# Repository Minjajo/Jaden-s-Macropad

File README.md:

# Jaden-s-Hackpad

This macropad has 16 keys, and right now it just acts as a numpad

This is what it looks like:

## PCB Design:
Here is a picture of my PCB:

Here is a picture of my schematic:

## CAD Design:
(Note: I only designed the case itself. The PCB STEP file was exported from KiCAD and the switches, keycaps, and XIAO were found on GRABCAD)
This is what the assembled hackpad looks like in Fusion:

This is what the case + PCB looks lke in Fusion:

## Bill of Materials:
- 1x SEEEDUINO XIAO RP2040
- 20x through-hole 1N4148 Diodes
- 16x MX-Style switches
- 16x white blank DSA keycaps
- 16x SK6812 MINI-E LEDs
- 4x M3x16mm screws
- Jaden's Custom PCB

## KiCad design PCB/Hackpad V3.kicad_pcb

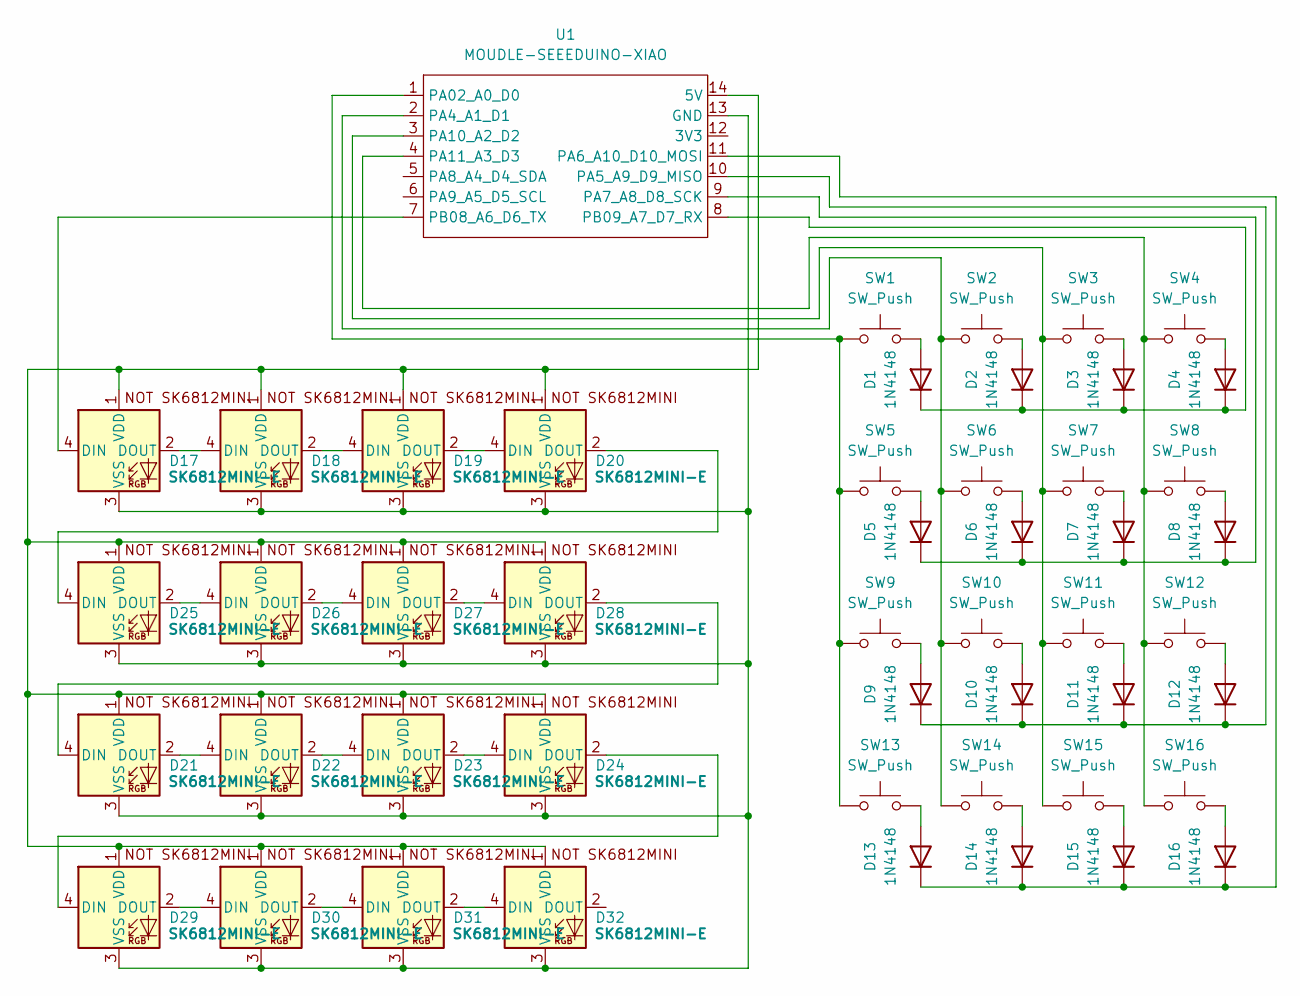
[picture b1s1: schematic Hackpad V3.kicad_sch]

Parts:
D1, D2, D3, D4, D5, D6, D7, D8, D9, D10, D11, D12, D13, D14, D15, D16: 1N4148; D_DO-35_SOD27_P7.62mm_Horizontal
D17, D18, D19, D20, D21, D22, D23, D24, D25, D26, D27, D28, D29, D30, D31, D32: SK6812MINI-E; SK6812MINI-E_fixed
SW1, SW2, SW3, SW4, SW5, SW6, SW7, SW8, SW9, SW10, SW11, SW12, SW13, SW14, SW15, SW16: SW_Push; SW_Cherry_MX_1.00u_PCB
U1: MOUDLE-SEEEDUINO-XIAO; XIAO-Generic-Hybrid-14P-2.54-21X17.8MM

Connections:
unnamed: D1.2 (A), SW1.2
unnamed: D1.1 (K), D2.1 (K), D3.1 (K), D4.1 (K), U1.8 (PB09_A7_D7_RX)
unnamed: D2.2 (A), SW2.2
unnamed: D3.2 (A), SW3.2
unnamed: D4.2 (A), SW4.2
unnamed: D5.2 (A), SW5.2
unnamed: D5.1 (K), D6.1 (K), D7.1 (K), D8.1 (K), U1.9 (PA7_A8_D8_SCK)
unnamed: D6.2 (A), SW6.2
unnamed: D7.2 (A), SW7.2
unnamed: D8.2 (A), SW8.2
unnamed: D9.2 (A), SW9.2
unnamed: D10.2 (A), SW10.2
unnamed: D9.1 (K), D10.1 (K), D11.1 (K), D12.1 (K), U1.10 (PA5_A9_D9_MISO)
unnamed: D11.2 (A), SW11.2
unnamed: D12.2 (A), SW12.2
unnamed: D13.2 (A), SW13.2
unnamed: D13.1 (K), D14.1 (K), D15.1 (K), D16.1 (K), U1.11 (PA6_A10_D10_MOSI)
unnamed: D14.2 (A), SW14.2
unnamed: D15.2 (A), SW15.2
unnamed: D16.2 (A), SW16.2
unnamed: D17.4 (DIN), U1.7 (PB08_A6_D6_TX)
unnamed: D17.2 (DOUT), D18.4 (DIN)
unnamed: D17.1 (VDD), D18.1 (VDD), D19.1 (VDD), D20.1 (VDD), D21.1 (VDD), D22.1 (VDD), D23.1 (VDD), D24.1 (VDD), D25.1 (VDD), D26.1 (VDD), D27.1 (VDD), D28.1 (VDD), D29.1 (VDD), D30.1 (VDD), D31.1 (VDD), D32.1 (VDD), U1.14 (5V)
unnamed: D17.3 (VSS), D18.3 (VSS), D19.3 (VSS), D20.3 (VSS), D21.3 (VSS), D22.3 (VSS), D23.3 (VSS), D24.3 (VSS), D25.3 (VSS), D26.3 (VSS), D27.3 (VSS), D28.3 (VSS), D29.3 (VSS), D30.3 (VSS), D31.3 (VSS), D32.3 (VSS), U1.13 (GND)
unnamed: D18.2 (DOUT), D19.4 (DIN)
unnamed: D19.2 (DOUT), D20.4 (DIN)
unnamed: D20.2 (DOUT), D25.4 (DIN)
unnamed: D21.4 (DIN), D28.2 (DOUT)
unnamed: D21.2 (DOUT), D22.4 (DIN)
unnamed: D22.2 (DOUT), D23.4 (DIN)
unnamed: D23.2 (DOUT), D24.4 (DIN)
unnamed: D24.2 (DOUT), D29.4 (DIN)
unnamed: D25.2 (DOUT), D26.4 (DIN)
unnamed: D26.2 (DOUT), D27.4 (DIN)
unnamed: D27.2 (DOUT), D28.4 (DIN)
unnamed: D29.2 (DOUT), D30.4 (DIN)
unnamed: D30.2 (DOUT), D31.4 (DIN)
unnamed: D31.2 (DOUT), D32.4 (DIN)
unnamed: SW1.1, SW5.1, SW9.1, SW13.1, U1.1 (PA02_A0_D0)
unnamed: SW2.1, SW6.1, SW10.1, SW14.1, U1.2 (PA4_A1_D1)
unnamed: SW3.1, SW7.1, SW11.1, SW15.1, U1.3 (PA10_A2_D2)
unnamed: SW4.1, SW8.1, SW12.1, SW16.1, U1.4 (PA11_A3_D3)

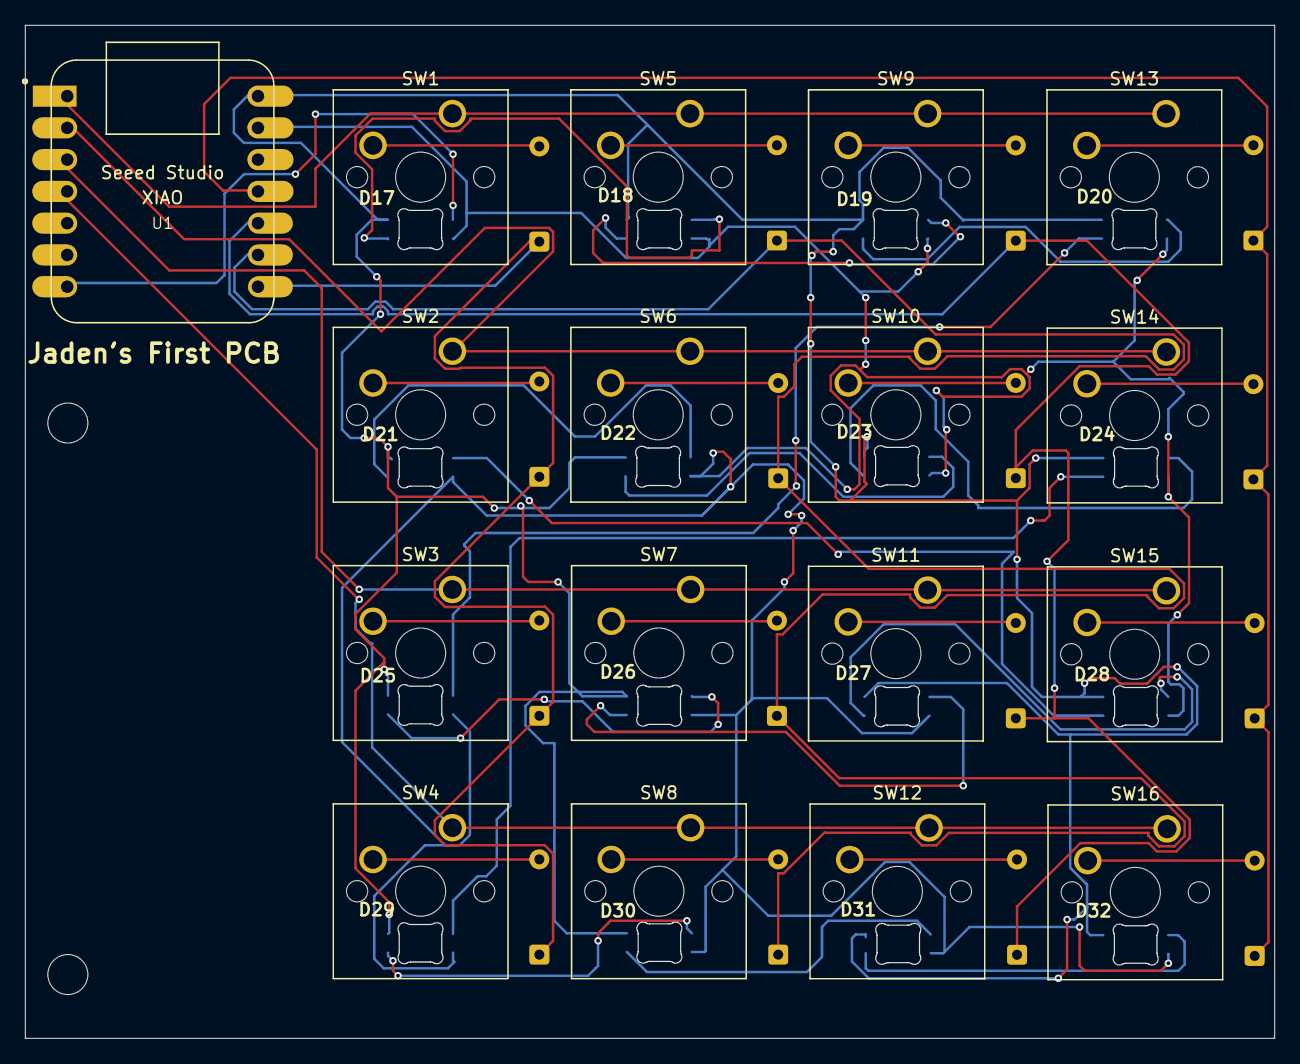
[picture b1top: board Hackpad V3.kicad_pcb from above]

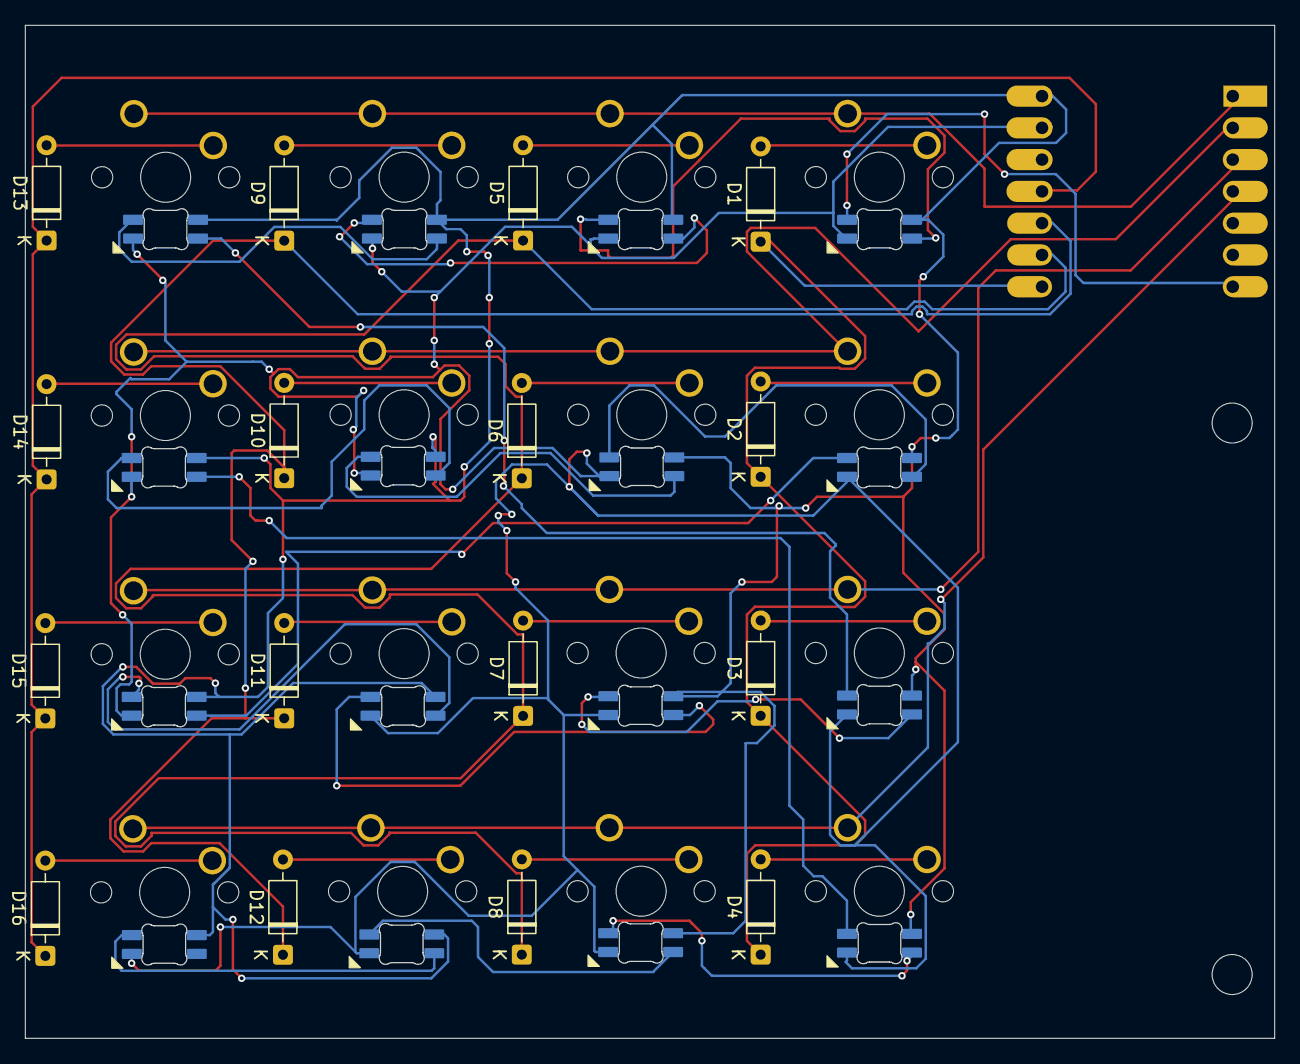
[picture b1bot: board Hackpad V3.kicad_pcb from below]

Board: 2 copper layers, 99.9 x 81.0 mm, 49 parts (16 on the bottom side), 42 nets.

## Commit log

2026-03-14 Update README with macropad description
    Added a brief description of the macropad.
2026-03-14 Add placeholder file
2026-03-14 Create placeholder
2026-03-14 Update README to clarify macropad functionality
2026-03-14 Add Bill of Materials section to README
2026-03-14 Update README with PCB design and schematic images
    Added PCB design images and schematic to README.
2026-03-14 Rename project to Jaden's Hackpad and enhance README
    Updated project name and added CAD design section with images.
2026-03-15 Rename Jaden's Hackpad V3.step to Jaden's Hackpad V3 (old).step
